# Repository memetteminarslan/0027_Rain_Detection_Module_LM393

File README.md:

# 0027_Rain_Detection_Module_LM393

You are seeing a large number of widely used rain detection modules in electronic development kits. More information coming soon...

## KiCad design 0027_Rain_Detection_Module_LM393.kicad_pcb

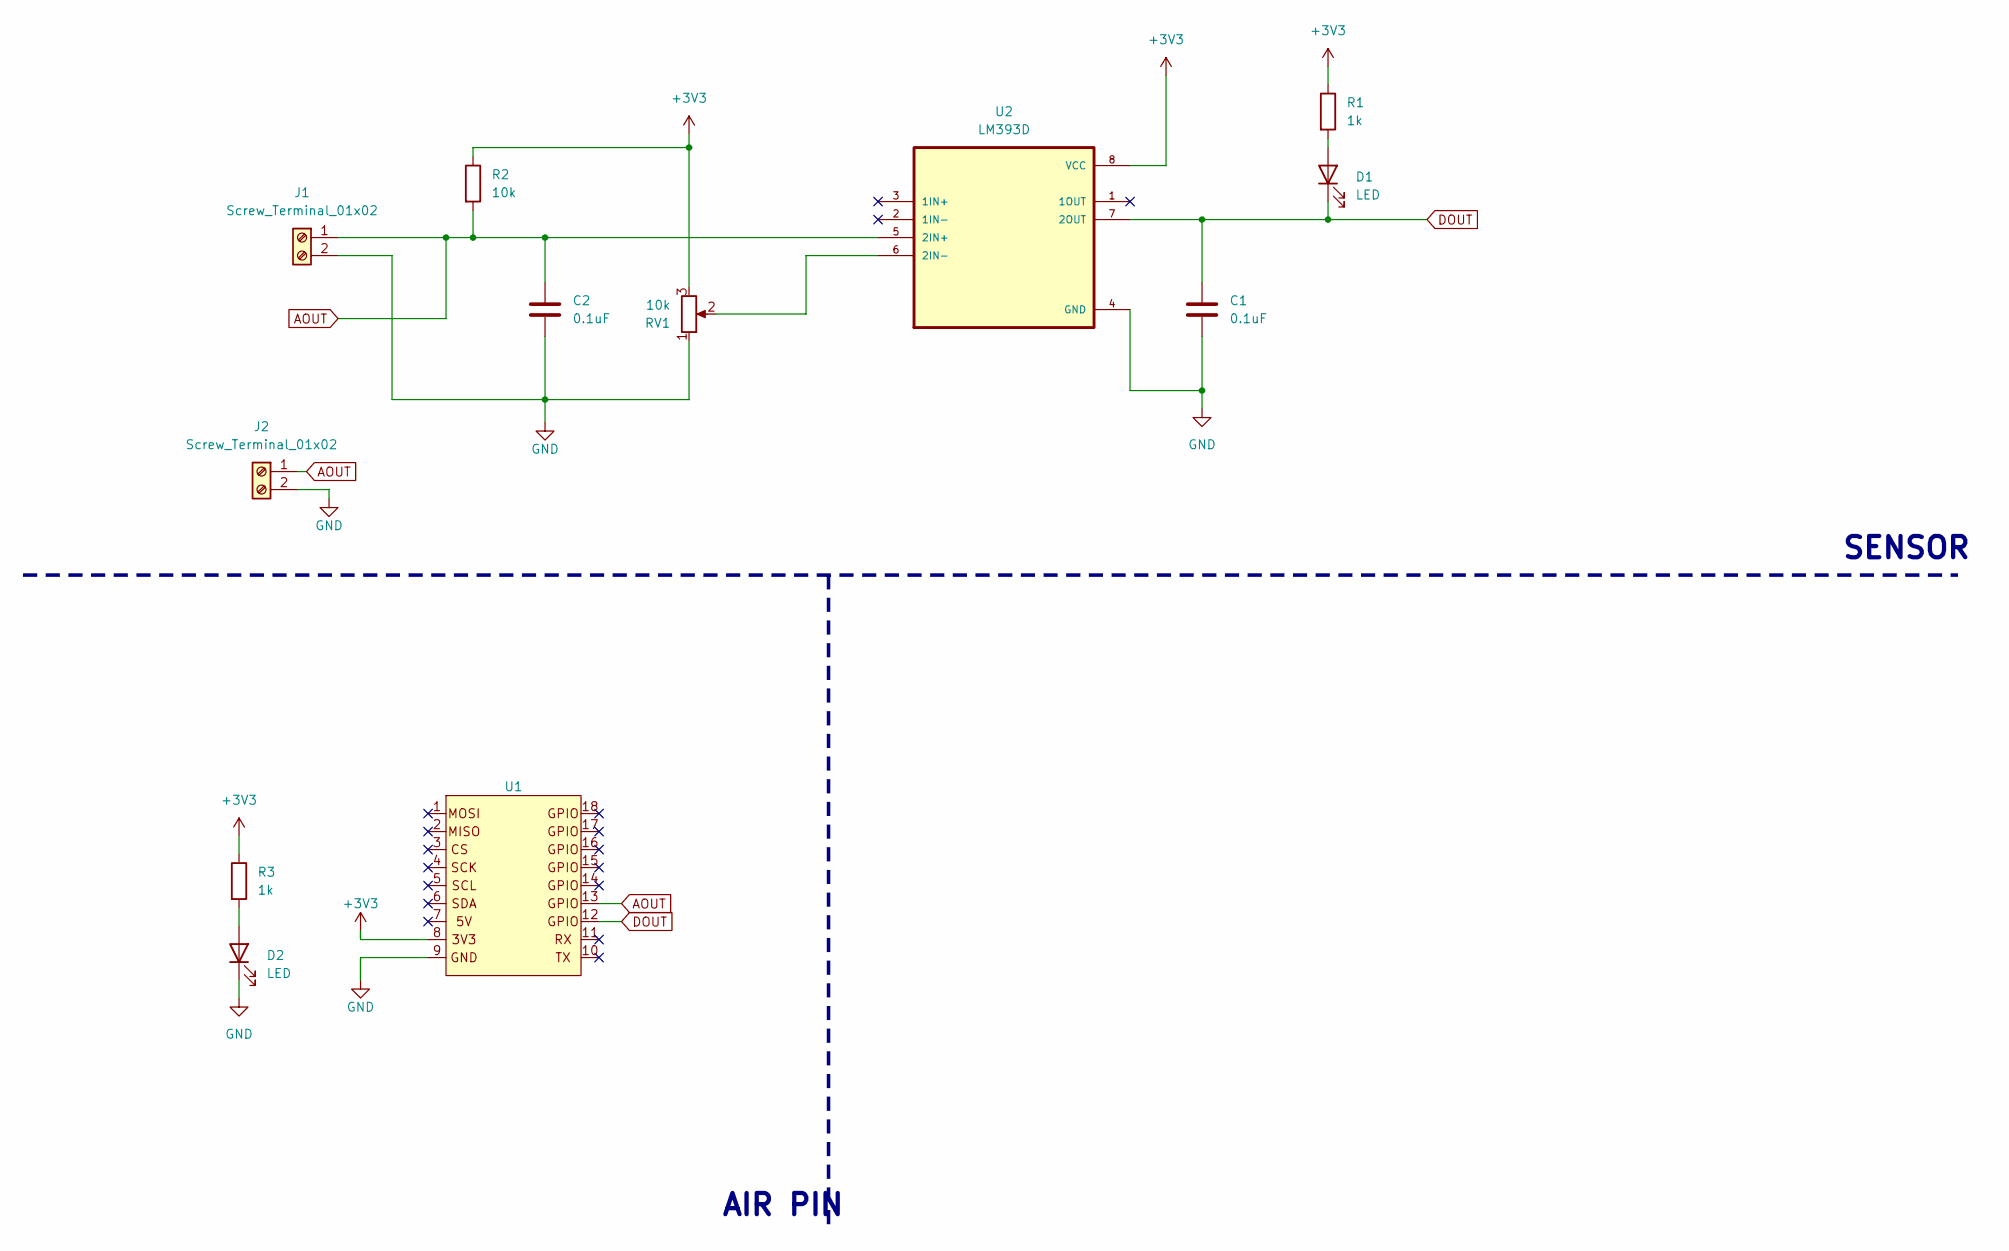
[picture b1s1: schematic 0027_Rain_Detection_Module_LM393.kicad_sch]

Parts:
C1, C2: 0.1uF; C_0805_2012Metric
D1, D2: LED; LED_0805_2012Metric
J1: Screw_Terminal_01x02; TerminalBlock_4Ucon_1x02_P3.50mm_Horizontal
J2: Screw_Terminal_01x02; rain
R1, R3: 1k; R_0805_2012Metric
R2: 10k; R_0805_2012Metric
RV1: 10k; 3362P_1
U1: pin_header
U2: LM393D; SOIC127P599X175-8N

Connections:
+3V3: R1.1, R2.1, R3.1, RV1.3, U1.8, U2.8 (VCC)
AOUT: C2.1, J1.1, J2.1, R2.2, U1.13, U2.5 (2IN+)
DOUT: C1.1, D1.1 (K), U1.12, U2.7 (2OUT)
GND: C1.2, C2.2, D2.1 (K), J1.2, J2.2, RV1.1, U1.9, U2.4 (GND)
unnamed: D1.2 (A), R1.2
unnamed: D2.2 (A), R3.2
unnamed: RV1.2, U2.6 (2IN-)

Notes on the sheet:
SENSOR
AIR PIN

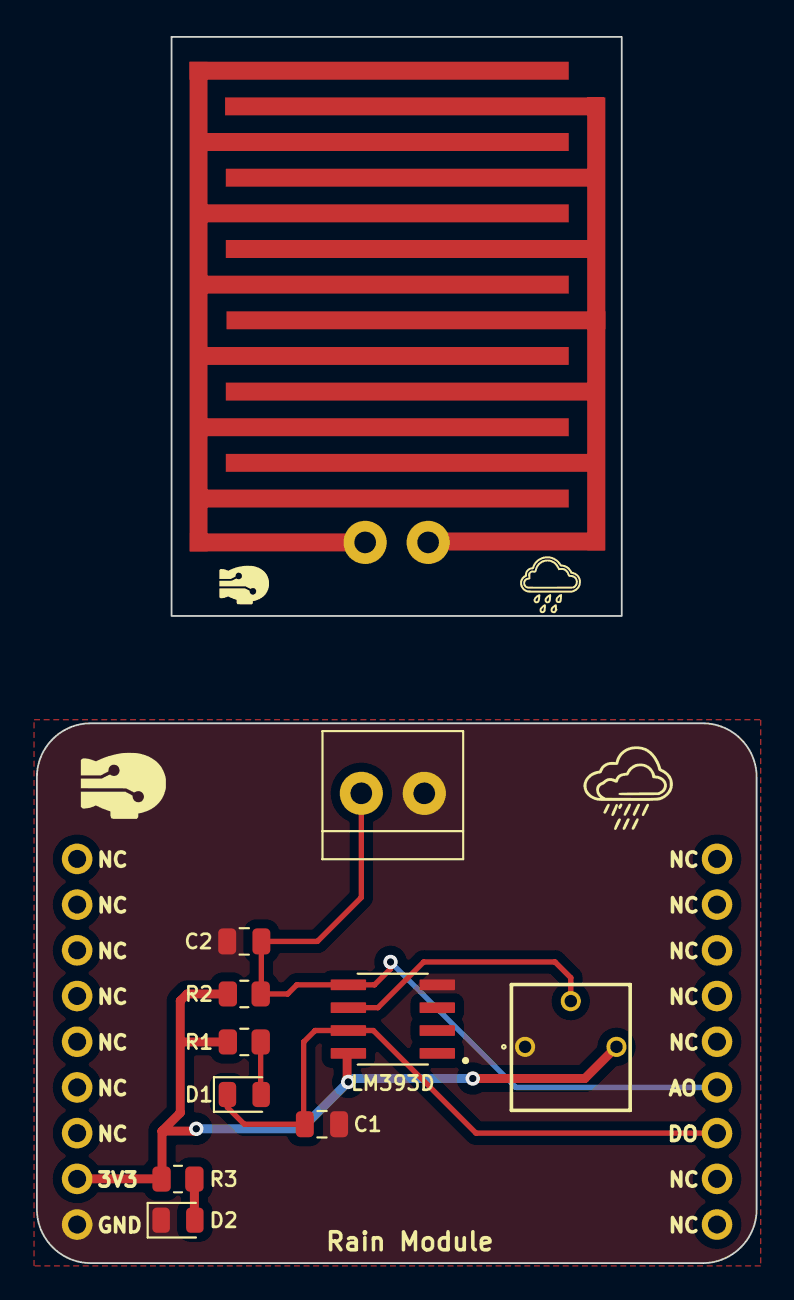
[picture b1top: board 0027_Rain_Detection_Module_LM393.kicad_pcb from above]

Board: 2 copper layers, 40.0 x 30.0 mm, 12 parts (0 on the bottom side), 7 nets.
